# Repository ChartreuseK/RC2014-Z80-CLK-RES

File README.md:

## A z80 + Clock + Reset Board for the RC2014 Bus

A simple z80 board with integrated clock circuit (can oscillator) and divider. A 555 timer circuit provides power on and on demand reset with a clean pulse. 

The 74HCT393 is optional if you don't wish to divide the clock, just add a jumper or link on the FULL speed pad below it and it'll not be used. There is a shared footprint for either DIP-14 or DIP-8 can oscillators. For DIP-8 align it to the right edge of the socket. The reset pulse length can be shortened by lowering the values of R1 and R2, or adjusting the capacitor values. The 10k value of the pullup resistors is also nominal, and will likely work fine from 1k to 10k

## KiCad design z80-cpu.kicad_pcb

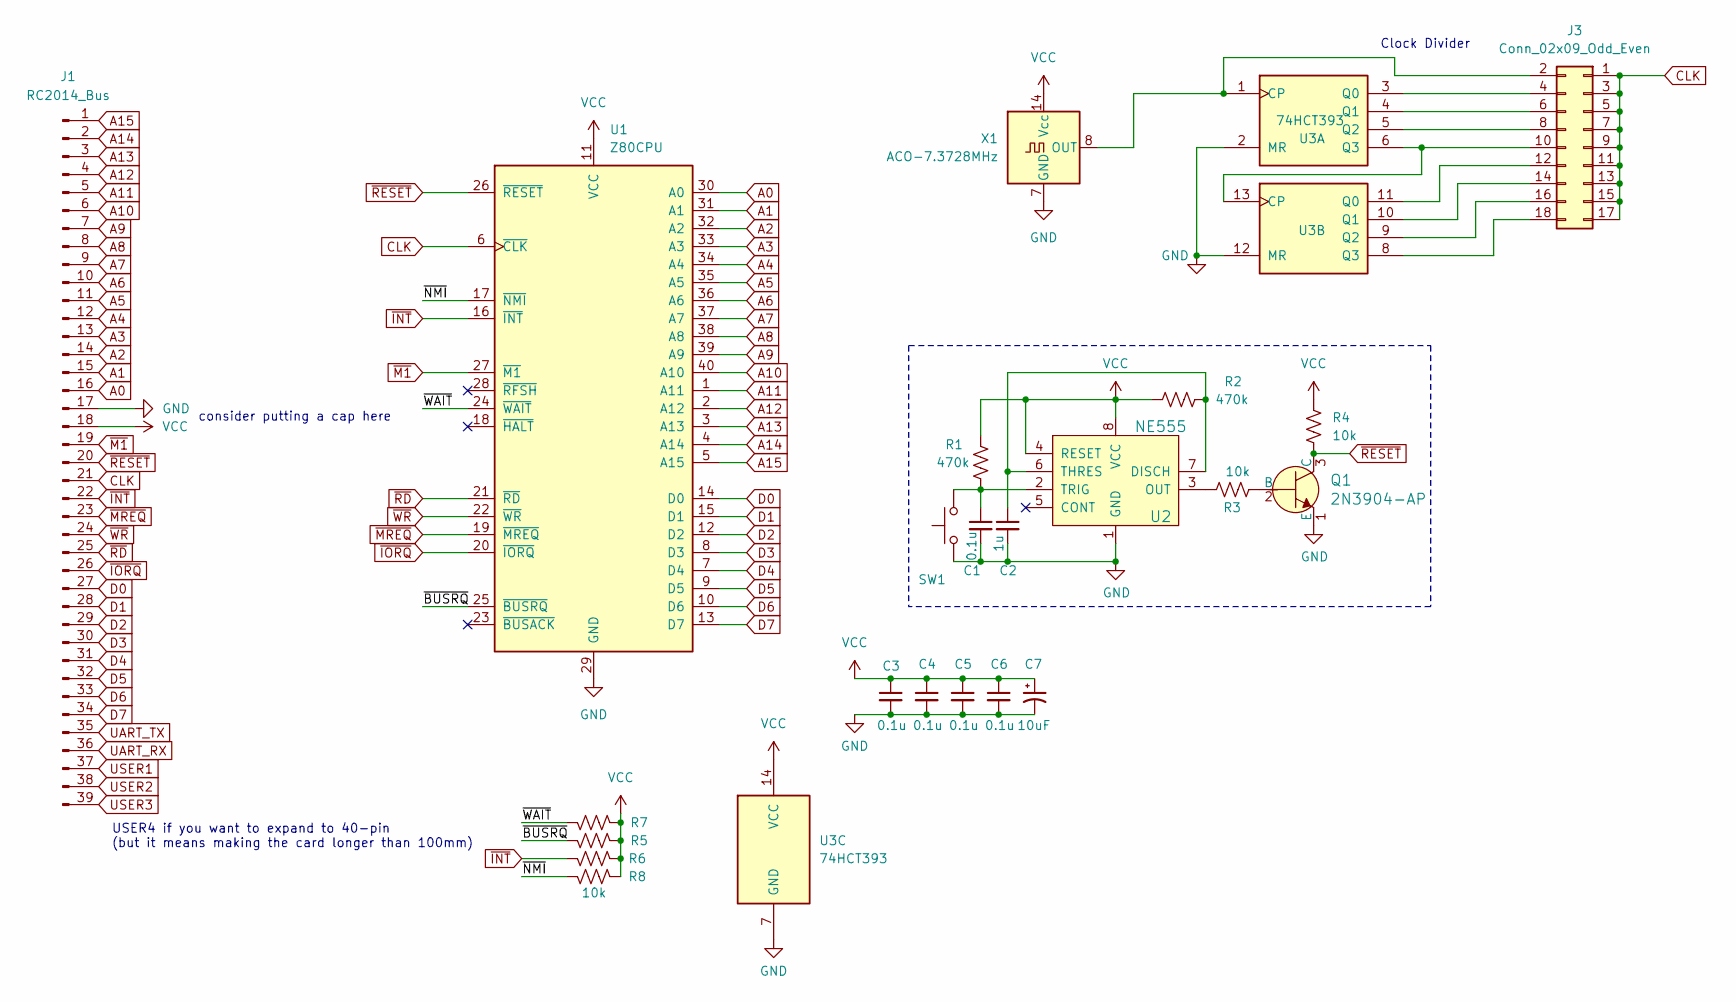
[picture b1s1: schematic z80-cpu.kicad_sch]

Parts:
C1, C3, C4, C5, C6: 0.1u; C_Disc_D4.3mm_W1.9mm_P5.00mm
C2: 1u; C_Disc_D4.3mm_W1.9mm_P5.00mm
C7: 10uF; CP_Radial_Tantal_D4.5mm_P2.50mm
J1: RC2014_Bus; PinHeader_1x39_P2.54mm_Vertical
J3: Conn_02x09_Odd_Even; PinHeader_2x09_P2.54mm_Vertical
Q1: 2N3904-AP; TO-92L_Inline_Wide; MPN 2N3904-AP; Digi-Key_PN 2N3904-APCT-ND
R1, R2: 470k; R_Axial_DIN0207_L6.3mm_D2.5mm_P10.16mm_Horizontal
R3, R4, R5, R6, R7, R8: 10k; R_Axial_DIN0207_L6.3mm_D2.5mm_P10.16mm_Horizontal
SW1: RESET; SW_PUSH_6mm
U1: Z80CPU; DIP-40_W15.24mm_Socket_LongPads
U2: NE555; DIP-8_W7.62mm_Socket_LongPads; MPN NE555P; Digi-Key_PN 296-1411-5-ND
U3: 74HCT393; DIP-14_W7.62mm_Socket_LongPads
X1: ACO-7.3728MHz; Oscillator_DIP-14_LargePads

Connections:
/~BUSRQ: R5.2, U1.25 (~BUSRQ)
/~NMI: R8.2, U1.17 (~NMI)
/~WAIT: R7.2, U1.24 (~WAIT)
A0: J1.16, U1.30 (A0)
A1: J1.15, U1.31 (A1)
A2: J1.14, U1.32 (A2)
A3: J1.13, U1.33 (A3)
A4: J1.12, U1.34 (A4)
A5: J1.11, U1.35 (A5)
A6: J1.10, U1.36 (A6)
A7: J1.9, U1.37 (A7)
A8: J1.8, U1.38 (A8)
A9: J1.7, U1.39 (A9)
A10: J1.6, U1.40 (A10)
A11: J1.5, U1.1 (A11)
A12: J1.4, U1.2 (A12)
A13: J1.3, U1.3 (A13)
A14: J1.2, U1.4 (A14)
A15: J1.1, U1.5 (A15)
CLK: J1.21, J3.1, J3.3, J3.5, J3.7, J3.9, J3.11, J3.13, J3.15, J3.17, U1.6 (~CLK)
D0: J1.27, U1.14 (D0)
D1: J1.28, U1.15 (D1)
D2: J1.29, U1.12 (D2)
D3: J1.30, U1.8 (D3)
D4: J1.31, U1.7 (D4)
D5: J1.32, U1.9 (D5)
D6: J1.33, U1.10 (D6)
D7: J1.34, U1.13 (D7)
GND: C1.2, C2.2, C3.2, C4.2, C5.2, C6.2, C7.2, J1.17, Q1.1 (E), SW1.1, U1.29 (GND), U2.1 (GND), U3.2 (MR), U3.7 (GND), U3.12 (MR), X1.7 (GND)
unnamed: J3.2, U3.1 (CP), X1.8 (OUT)
unnamed: J3.4, U3.3 (Q0)
unnamed: J3.6, U3.4 (Q1)
unnamed: J3.8, U3.5 (Q2)
unnamed: J3.10, U3.6 (Q3), U3.13 (CP)
unnamed: J3.12, U3.11 (Q0)
unnamed: J3.14, U3.10 (Q1)
unnamed: J3.16, U3.9 (Q2)
unnamed: J3.18, U3.8 (Q3)
unnamed: Q1.2 (B), R3.2
unnamed: C2.1, R2.1, U2.6 (THRES), U2.7 (DISCH)
unnamed: R3.1, U2.3 (OUT)
unnamed: C1.1, R1.2, SW1.2, U2.2 (TRIG)
UART_RX: J1.36
UART_TX: J1.35
USER1: J1.37
USER2: J1.38
USER3: J1.39
VCC: C3.1, C4.1, C5.1, C6.1, C7.1, J1.18, R1.1, R2.2, R4.1, R5.1, R6.1, R7.1, R8.1, U1.11 (VCC), U2.4 (RESET), U2.8 (VCC), U3.14 (VCC), X1.14 (Vcc)
~INT: J1.22, R6.2, U1.16 (~INT)
~IORQ: J1.26, U1.20 (~IORQ)
~M1: J1.19, U1.27 (~M1)
~MREQ: J1.23, U1.19 (~MREQ)
~RD: J1.25, U1.21 (~RD)
~RESET: J1.20, Q1.3 (C), R4.2, U1.26 (~RESET)
~WR: J1.24, U1.22 (~WR)

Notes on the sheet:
Clock Divider
consider putting a cap here
USER4 if you want to expand to 40-pin (but it means making the card longer than 100mm)

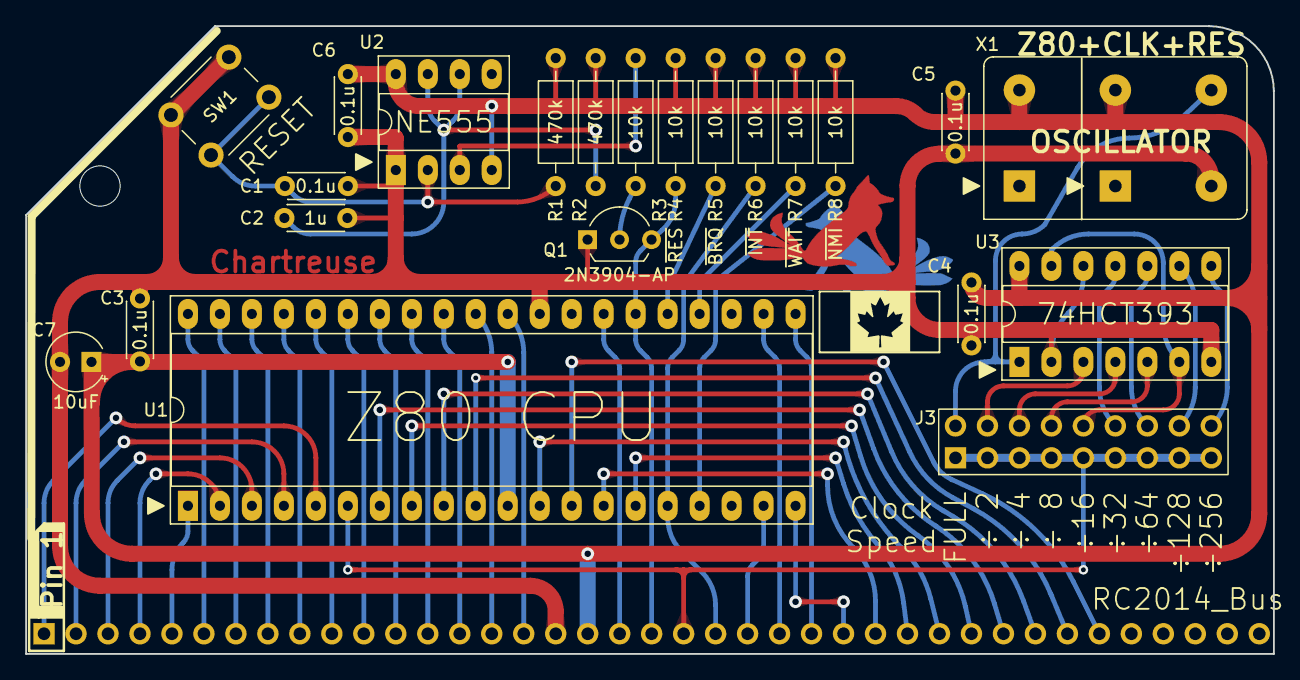
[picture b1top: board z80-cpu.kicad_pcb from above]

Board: 2 copper layers, 99.1 x 49.9 mm, 23 parts (0 on the bottom side), 50 nets.

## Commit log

2024-06-25 Initial commit, simple z80 sbc with onboard clock generator and reset circuitry for rc2014
2024-06-25 Changed bus labels to global labels, made uppercase
2024-06-25 Added gitignore
2024-06-25 Added GPLv3 License
2024-06-25 Added board images
2024-06-25 Added initial readme
2024-06-25 Fixed typo in image embed
2024-06-25 Added some substitutions to readme
2024-06-25 Fixed missing reset pullup, and slightly broken schematic after changing header labels. Rev 2
